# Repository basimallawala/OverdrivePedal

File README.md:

# Overdrive Guitar Pedal

A through-hole guitar overdrive pedal designed in KiCad. Op-amp gain stage with diode soft-clipping, a tone control, a volume control, true-bypass switching with an indicator LED, and battery or DC power. Everything (pots, jacks, LED) mounts directly to the PCB, so the board sits behind the enclosure face with nothing but the footswitch wired by hand.

## Features

- Non-inverting TL072 gain stage with symmetric 1N4148 clipping
- Gain, Tone and Volume controls
- True bypass via a 3PDT footswitch, with an LED that lights only when the effect is engaged
- Powered by a 9V battery or a DC jack (the switched jack disconnects the battery when an adapter is plugged in)
- Battery power switches on automatically when a cable is plugged into the input jack (stereo jack ring wired to battery negative)
- Fully through-hole, hand-solderable

## Circuit overview

Signal path, left to right:

1. **Input**: R6 (10k) and C4 (22nF) AC-couple the guitar into the op-amp's non-inverting input. R8 (1M) to ground gives the input a discharge path.
2. **Bias**: R4/R3 (10k/10k) from the 9V rail make a 4.5V virtual ground, filtered by C3 (47uF). R5 (1M) feeds that reference into the op-amp input so the signal rides on 4.5V.
3. **Gain stage (U1A)**: RV1 (500k) in parallel with C6 (100pF) sets the feedback resistance against the R2 (1k) / C5 (220nF) ground leg. D1 and D2 (1N4148, antiparallel) across the feedback network clip the output.
4. **Tone**: RV2 (10k) with C1 (22nF) forms a variable low-pass after the gain stage.
5. **Output**: C7 (0.1uF) blocks the 4.5V DC offset, R7 (1M) pulls the node to ground, and RV3 (100k) sets output volume.

The unused op-amp half (U1B) is tied off, and C8 (0.1uF) decouples the TL072 supply.

## Controls

| Ref | Control | Value | Taper | Part |
|---|---|---|---|---|
| RV1 | Gain | 500k | Linear | Bourns PTV09A-4020U-B504 |
| RV2 | Tone | 10k | Linear | Bourns PTV09A-4020S-B103 |
| RV3 | Volume | 100k | Log (audio) | Bourns PTV09A-4020S-A104 |

## Bypass wiring

The footswitch is wired off-board to a 1x9 header (SW1). Each pole's common is the middle lug of its column:

| Pole | Common | Engaged | Bypass |
|---|---|---|---|
| A | IN | OV_IN (into effect) | jumper to pole B |
| B | OUT | OV_OUT (from effect) | jumper to pole A |
| C | LED cathode | GND | no connect |

IN is the guitar signal, OUT goes to the amp, and OV_IN / OV_OUT are the effect's input and output.

## Bill of materials

The full list is in [`BOM.csv`](BOM.csv). Key parts:

| Ref | Part | Notes |
|---|---|---|
| U1 | TL072 | DIP-8 (through-hole) package |
| D1, D2 | 1N4148 | DO-35 |
| D3 | 5mm red LED | |
| J4, J5 | Neutrik NMJ6HFD2 | Switched 1/4" stereo jacks (input and output) |
| J1 | Tensility 54-00130 | 5.5 x 2.5mm right-angle DC jack |
| SW1 | 3PDT stomp switch | Panel-mounted, wired to the SW1 header |
| RV1-RV3 | Bourns PTV09A | See Controls table |
| Passives | Axial 1/4W resistors, radial ceramic and electrolytic caps | All through-hole |

## Mechanical notes

- Pots, jacks and the LED are PCB-mounted, so the board layout and the enclosure drilling have to match exactly. Take hole positions from the PCB, not separately.
- The PCB mounts on standoffs with M3 screws (3.2mm clearance holes, non-plated).
- The footswitch mounts to the enclosure with its bushing and nut; only its 9 wires connect to the board.
- The enclosure is 3D printed. Use heat-set M3 inserts rather than printed threads for any screw that gets removed more than once.
- Enclosure size is driven by the artwork, so confirm dimensions before finalizing the board outline.

## Simulation

The overdrive stage can be simulated with KiCad's built-in ngspice simulator. Tips from the build:

- Simulate only the Overdrive and DC Bias sheets. Exclude connectors and the footswitch, which have no SPICE models.
- Replace the input with a VSIN source (for example 500mV amplitude, 1kHz) on the OV_IN net.
- Give the TL072 a SPICE model and check its pin assignments for every unit, including the power unit.
- Potentiometers simulate as fixed resistors, so set each wiper position manually.
- AC sweeps show frequency response only, not clipping. Use transient analysis for clipping.

## Repository contents

Adjust this list to match the repo.

- `UmarPedal.kicad_pro`, `UmarPedal.kicad_sch`, `UmarPedal.kicad_pcb`: KiCad project, schematic and board
- `BOM.csv`: bill of materials exported from KiCad
- Custom symbols and footprints for the Tensility 54-00130, Neutrik NMJ6HFD2 and Bourns PTV09A parts

Designed with KiCad 10.

## Known TODOs

- Confirm U1 is ordered as a DIP-8 part (for example TL072CP), not the SOIC variant.
- Make sure RV1, RV2 and RV3 carry their own values and footprints in the schematic so the BOM lists three distinct pots.
- Add the 1x9 header part that matches the SW1 footprint.
- Confirm the DC jack wiring and polarity against your power supply (the pedal standard is center-negative).
- Consider reverse-polarity protection on the power input.
- Check that the C6 part (rated 3kV) physically fits its footprint, or switch to a 50V 100pF ceramic.

## Build notes

1. Solder the low-profile parts first (resistors, diodes), then caps, the IC socket, and finally the pots, jacks and LED.
2. Wire the footswitch to the SW1 header following the bypass table above.
3. Test with a 9V supply before closing the enclosure. The 4.5V bias node should read about 4.5V.

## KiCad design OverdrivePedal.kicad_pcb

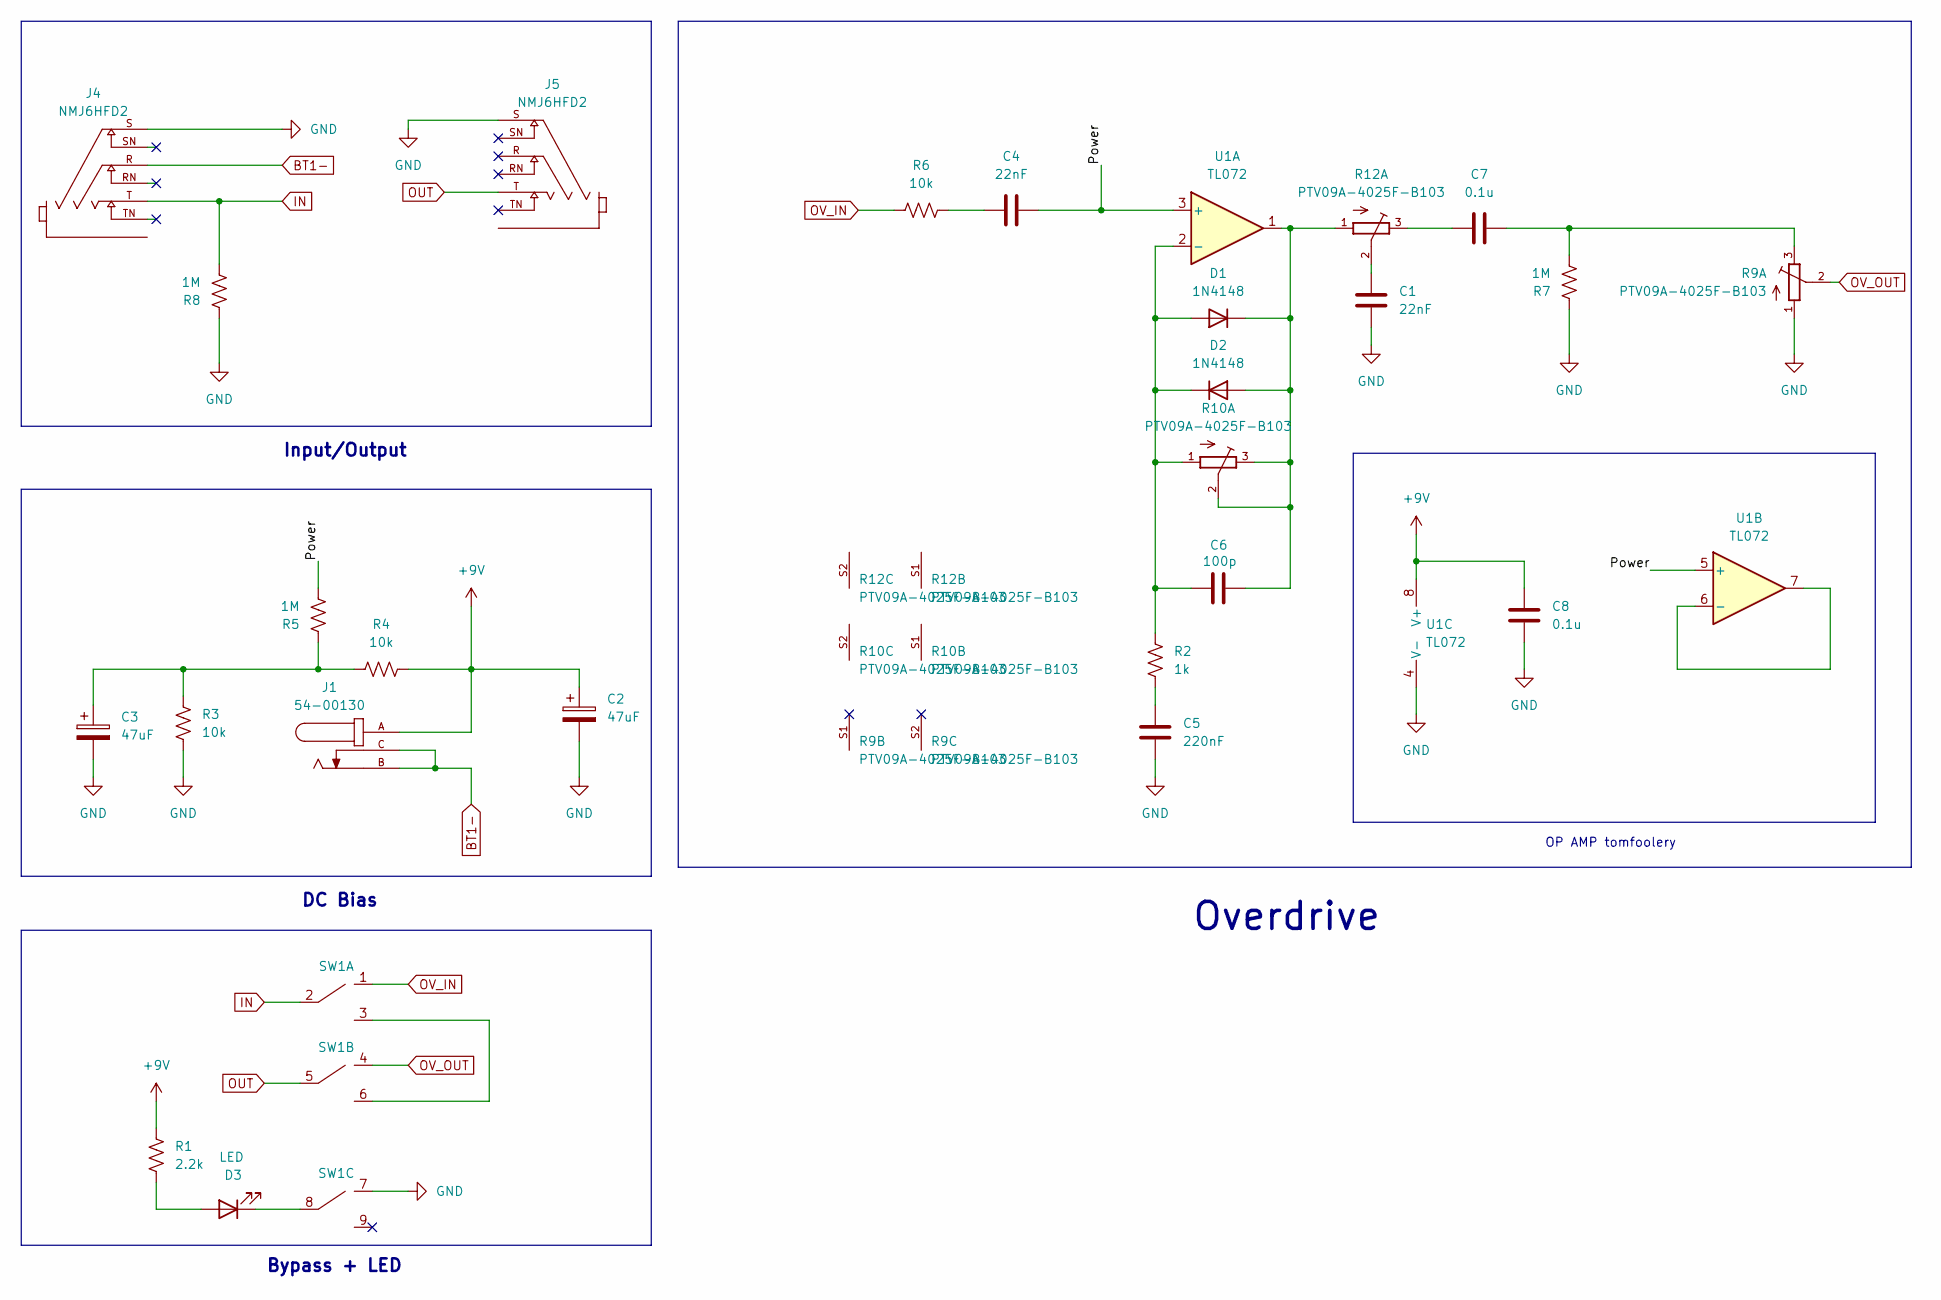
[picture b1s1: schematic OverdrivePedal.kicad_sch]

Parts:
C1, C4: 22nF; C_Disc_D5.0mm_W2.5mm_P5.00mm
C2, C3: 47uF; CP_Radial_D5.0mm_P2.00mm
C5: 220nF; C_Disc_D5.0mm_W2.5mm_P5.00mm
C6: 100p; C_Disc_D5.0mm_W2.5mm_P5.00mm
C7, C8: 0.1u; C_Disc_D5.0mm_W2.5mm_P5.00mm
D1, D2: 1N4148; D_DO-35_SOD27_P7.62mm_Horizontal
D3: LED; LED_D5.0mm
J1: 54-00130; TENSILITY_54-00130; PARTREV A
J4, J5: NMJ6HFD2; NEUTRIK_NMJ6HFD2; PARTREV 26.02.2021
R1: 2.2k; R_Axial_DIN0207_L6.3mm_D2.5mm_P10.16mm_Horizontal
R2: 1k; R_Axial_DIN0207_L6.3mm_D2.5mm_P10.16mm_Horizontal
R3, R4, R6: 10k; R_Axial_DIN0207_L6.3mm_D2.5mm_P10.16mm_Horizontal
R5, R7, R8: 1M; R_Axial_DIN0207_L6.3mm_D2.5mm_P10.16mm_Horizontal
R9, R10, R12: PTV09A-4025F-B103
SW1: PinSocket_1x09_P2.54mm_Vertical
U1: TL072; DIP-8_W7.62mm

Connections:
+9V: C2.1, C8.1, J1.A, R1.1, R4.2, U1.8 (V+)
/Power: C4.2, R5.1, U1.3 (+), U1.5 (+)
BT1-: J1.B, J1.C, J4.R
GND: C1.2, C2.2, C3.2, C5.2, C8.2, J4.S, J5.S, R3.2, R7.2, R8.2, R9.1, SW1.7, U1.4 (V-)
IN: J4.T, R8.1, SW1.2
unnamed: C1.1, R12.2
unnamed: C3.1, R3.1, R4.1, R5.2
unnamed: C4.1, R6.1
unnamed: C5.1, R2.2
unnamed: C7.1, R12.3
unnamed: C7.2, R7.1, R9.3
unnamed: C6.1, D1.2 (A), D2.1 (K), R2.1, R10.1, U1.2 (-)
unnamed: C6.2, D1.1 (K), D2.2 (A), R10.2, R10.3, R12.1, U1.1
unnamed: D3.2 (A), R1.2
unnamed: D3.1 (K), SW1.8
unnamed: SW1.3, SW1.6
unnamed: U1.6 (-), U1.7
OUT: J5.T, SW1.5
OV_IN: R6.2, SW1.1
OV_OUT: R9.2, SW1.4

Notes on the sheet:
OP AMP tomfoolery
Overdrive
Input/Output
Bypass + LED
DC Bias

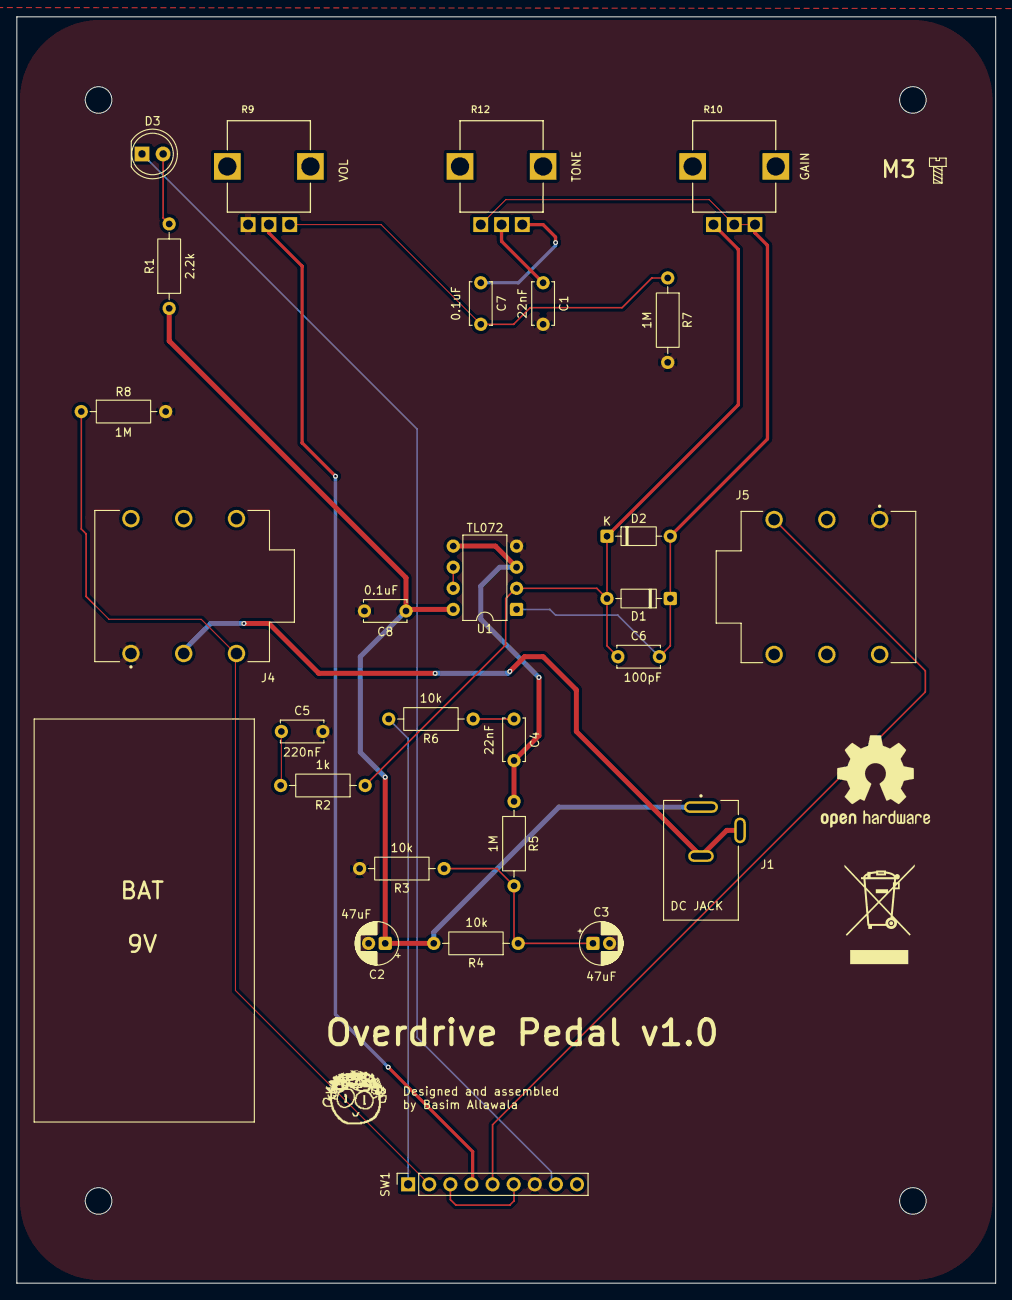
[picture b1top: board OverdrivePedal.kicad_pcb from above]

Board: 4 copper layers, 117.8 x 152.4 mm, 27 parts (0 on the bottom side), 20 nets.
